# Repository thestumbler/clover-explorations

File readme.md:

# Explorations of a Motherboard for Scott Baker's Clover Computer

Ref: Scott Baker's Z8000 Clover Computer
* [Project site](https://www.smbaker.com/scotts-z8000-cp-m-8000-clover-computer)
* [GitHub repo](https://github.com/sbelectronics/z8000)

Just playing around, seeing if there is any geometric regularity which
could be exploited to make this layout easier. It looks pretty, but I'm
not sure it would perform any better than the original. 

No signal names assigned other than ground and VCC. Originally I put
power and ground on two inner layers, but realized they could easily be
put on the perimeter of the outer layers.

* Done in Kicad v6. 
  - Schematics printed out as [PDF](z8000-sch.pdf) / [PNG](z8000-sch.png)
  - Layout as two PNG files, [TOP](z8000-top.png) / [BOT](z8000-bot.png)

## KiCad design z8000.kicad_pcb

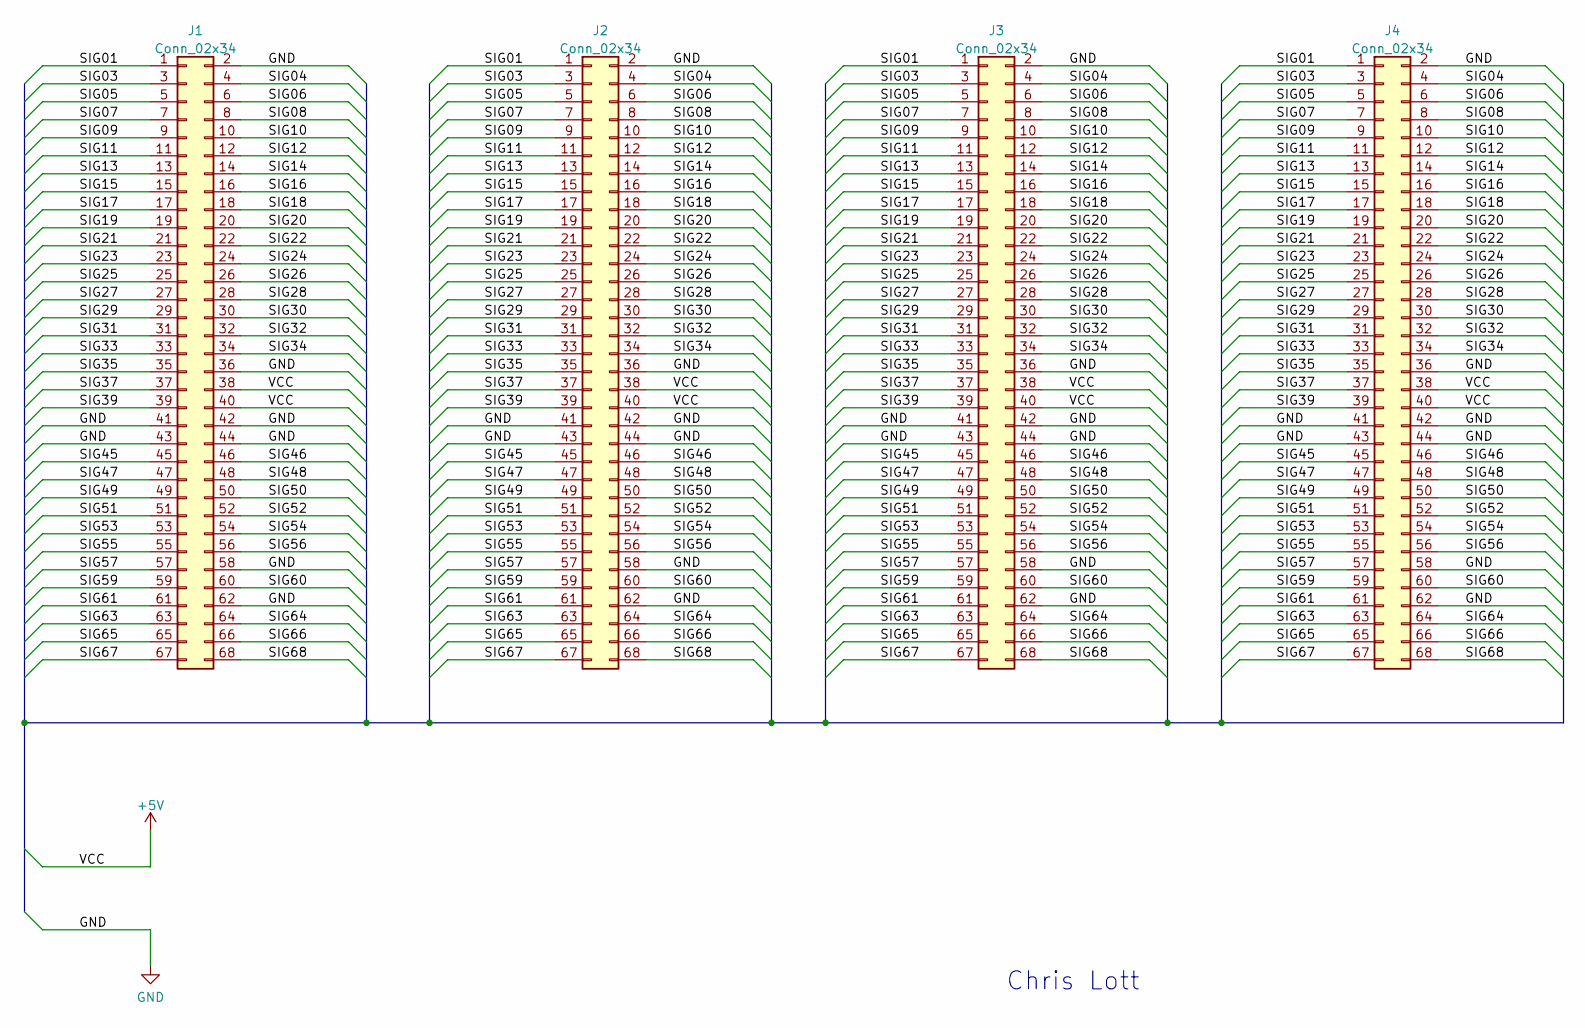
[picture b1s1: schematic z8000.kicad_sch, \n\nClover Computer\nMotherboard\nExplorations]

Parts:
J1, J2, J3, J4: Conn_02x34; PinSocket_2x34_P2.54mm_Horizontal

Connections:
+5V: J1.38, J1.40, J2.38, J2.40, J3.38, J3.40, J4.38, J4.40
/SIG01: J1.1, J2.1, J3.1, J4.1
/SIG03: J1.3, J2.3, J3.3, J4.3
/SIG04: J1.4, J2.4, J3.4, J4.4
/SIG05: J1.5, J2.5, J3.5, J4.5
/SIG06: J1.6, J2.6, J3.6, J4.6
/SIG07: J1.7, J2.7, J3.7, J4.7
/SIG08: J1.8, J2.8, J3.8, J4.8
/SIG09: J1.9, J2.9, J3.9, J4.9
/SIG10: J1.10, J2.10, J3.10, J4.10
/SIG11: J1.11, J2.11, J3.11, J4.11
/SIG12: J1.12, J2.12, J3.12, J4.12
/SIG13: J1.13, J2.13, J3.13, J4.13
/SIG14: J1.14, J2.14, J3.14, J4.14
/SIG15: J1.15, J2.15, J3.15, J4.15
/SIG16: J1.16, J2.16, J3.16, J4.16
/SIG17: J1.17, J2.17, J3.17, J4.17
/SIG18: J1.18, J2.18, J3.18, J4.18
/SIG19: J1.19, J2.19, J3.19, J4.19
/SIG20: J1.20, J2.20, J3.20, J4.20
/SIG21: J1.21, J2.21, J3.21, J4.21
/SIG22: J1.22, J2.22, J3.22, J4.22
/SIG23: J1.23, J2.23, J3.23, J4.23
/SIG24: J1.24, J2.24, J3.24, J4.24
/SIG25: J1.25, J2.25, J3.25, J4.25
/SIG26: J1.26, J2.26, J3.26, J4.26
/SIG27: J1.27, J2.27, J3.27, J4.27
/SIG28: J1.28, J2.28, J3.28, J4.28
/SIG29: J1.29, J2.29, J3.29, J4.29
/SIG30: J1.30, J2.30, J3.30, J4.30
/SIG31: J1.31, J2.31, J3.31, J4.31
/SIG32: J1.32, J2.32, J3.32, J4.32
/SIG33: J1.33, J2.33, J3.33, J4.33
/SIG34: J1.34, J2.34, J3.34, J4.34
/SIG35: J1.35, J2.35, J3.35, J4.35
/SIG37: J1.37, J2.37, J3.37, J4.37
/SIG39: J1.39, J2.39, J3.39, J4.39
/SIG45: J1.45, J2.45, J3.45, J4.45
/SIG46: J1.46, J2.46, J3.46, J4.46
/SIG47: J1.47, J2.47, J3.47, J4.47
/SIG48: J1.48, J2.48, J3.48, J4.48
/SIG49: J1.49, J2.49, J3.49, J4.49
/SIG50: J1.50, J2.50, J3.50, J4.50
/SIG51: J1.51, J2.51, J3.51, J4.51
/SIG52: J1.52, J2.52, J3.52, J4.52
/SIG53: J1.53, J2.53, J3.53, J4.53
/SIG54: J1.54, J2.54, J3.54, J4.54
/SIG55: J1.55, J2.55, J3.55, J4.55
/SIG56: J1.56, J2.56, J3.56, J4.56
/SIG57: J1.57, J2.57, J3.57, J4.57
/SIG59: J1.59, J2.59, J3.59, J4.59
/SIG60: J1.60, J2.60, J3.60, J4.60
/SIG61: J1.61, J2.61, J3.61, J4.61
/SIG63: J1.63, J2.63, J3.63, J4.63
/SIG64: J1.64, J2.64, J3.64, J4.64
/SIG65: J1.65, J2.65, J3.65, J4.65
/SIG66: J1.66, J2.66, J3.66, J4.66
/SIG67: J1.67, J2.67, J3.67, J4.67
/SIG68: J1.68, J2.68, J3.68, J4.68
GND: J1.2, J1.36, J1.41, J1.42, J1.43, J1.44, J1.58, J1.62, J2.2, J2.36, J2.41, J2.42, J2.43, J2.44, J2.58, J2.62, J3.2, J3.36, J3.41, J3.42, J3.43, J3.44, J3.58, J3.62, J4.2, J4.36, J4.41, J4.42, J4.43, J4.44, J4.58, J4.62

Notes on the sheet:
Chris Lott

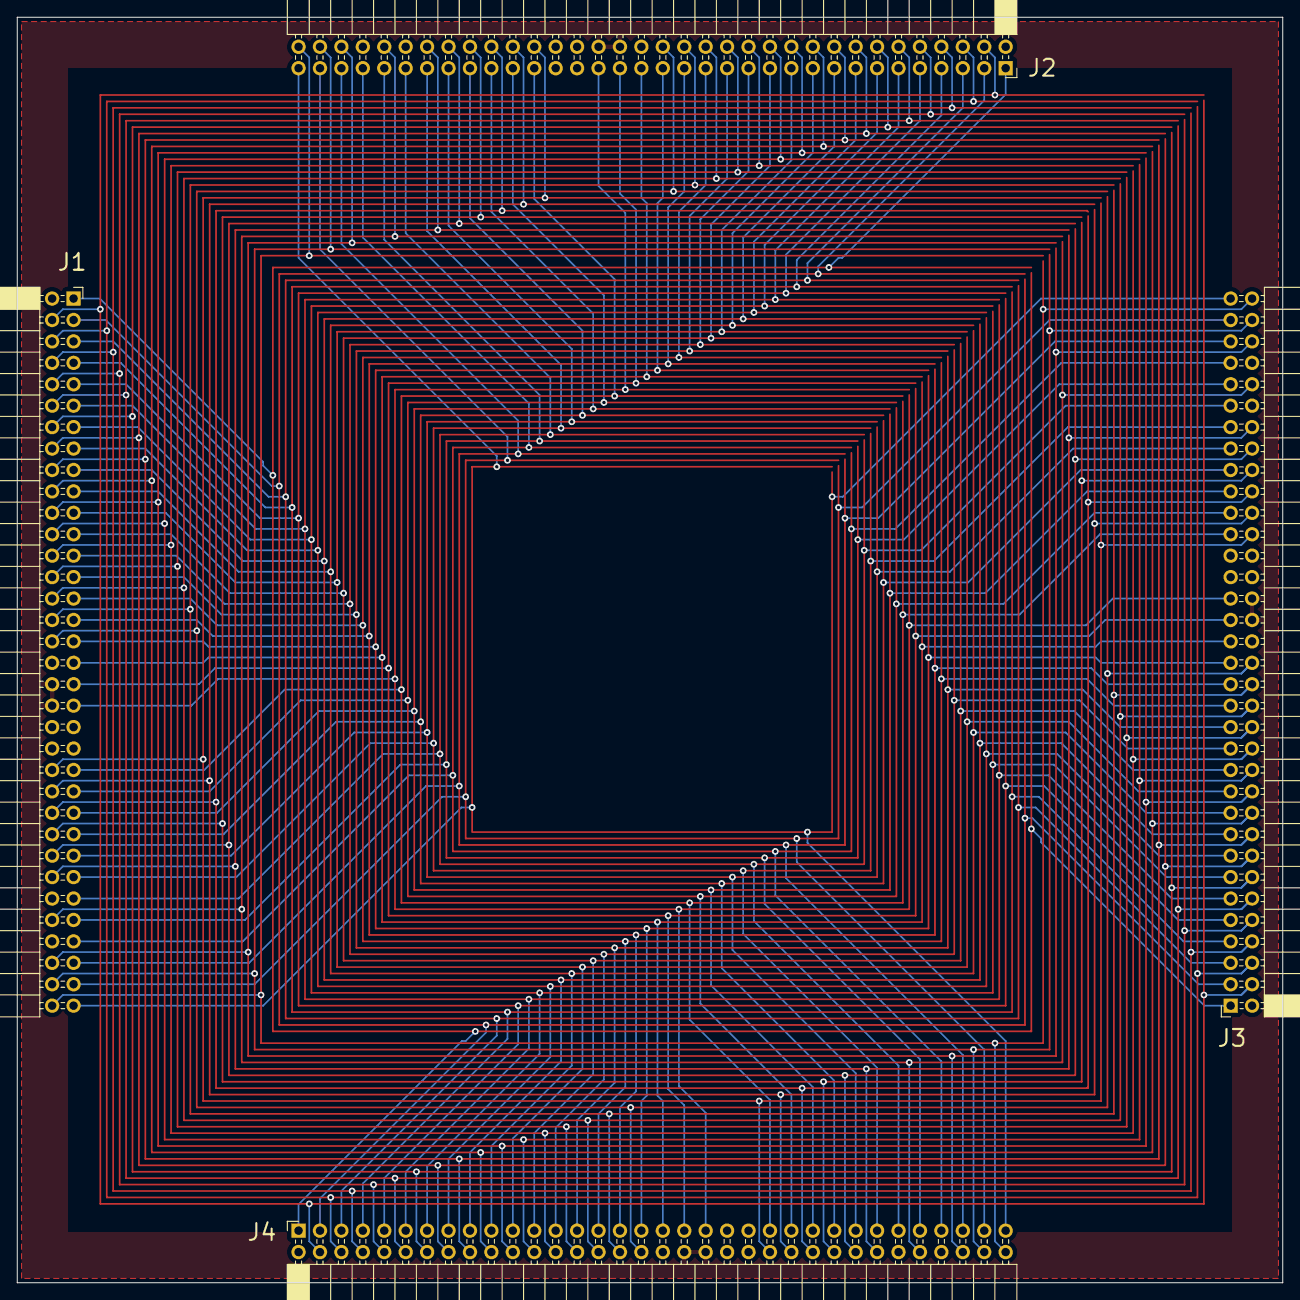
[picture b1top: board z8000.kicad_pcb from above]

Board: 4 copper layers, 150.0 x 150.0 mm, 4 parts (0 on the bottom side), 60 nets.

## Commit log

2022-08-21 added links to readme
2022-08-21 edited links
2022-08-21 typo
